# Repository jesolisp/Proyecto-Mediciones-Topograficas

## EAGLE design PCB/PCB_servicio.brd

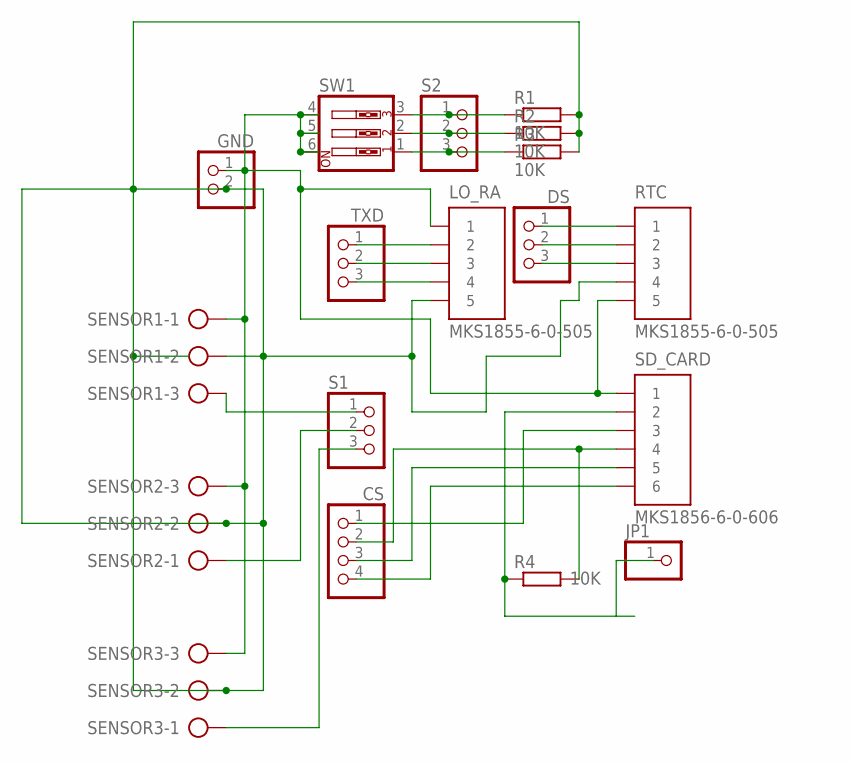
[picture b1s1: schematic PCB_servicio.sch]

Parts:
CS: PINHD-1X4; 1X04
DS: PINHD-1X3; 1X03
GND: PINHD-1X2; 1X02
JP1: PINHD-1X1; 1X01
LO_RA: MKS1855-6-0-505
R1, R2, R3, R4: 10K; 0207/12
RTC: MKS1855-6-0-505
S1, S2: PINHD-1X3; 1X03
SD_CARD: MKS1856-6-0-606
SENSOR1, SENSOR2, SENSOR3: AK500/3
SW1: SW_DIP-3; EDG-03
TXD: PINHD-1X3; 1X03

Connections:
unnamed: GND.1, LO_RA.1, RTC.5, SD_CARD.1, SENSOR1.1, SENSOR2.3, SENSOR3.3, SW1.4, SW1.5, SW1.6
unnamed: GND.2, LO_RA.5, R1.2, R2.2, R3.2, RTC.4, SENSOR1.2, SENSOR2.2, SENSOR3.2
unnamed: S1.1, SENSOR1.3
unnamed: S1.2, SENSOR2.1
unnamed: S1.3, SENSOR3.1
unnamed: R1.1, S2.1, SW1.3
unnamed: R2.1, S2.2, SW1.2
unnamed: R3.1, S2.3, SW1.1
unnamed: LO_RA.2, TXD.1
unnamed: LO_RA.3, TXD.2
unnamed: LO_RA.4, TXD.3
unnamed: CS.3, SD_CARD.5
unnamed: CS.4, SD_CARD.6
unnamed: CS.2, R4.2, SD_CARD.4
unnamed: CS.1, SD_CARD.3
unnamed: JP1.1, R4.1, SD_CARD.2
unnamed: DS.1, RTC.1
unnamed: DS.2, RTC.2
unnamed: DS.3, RTC.3

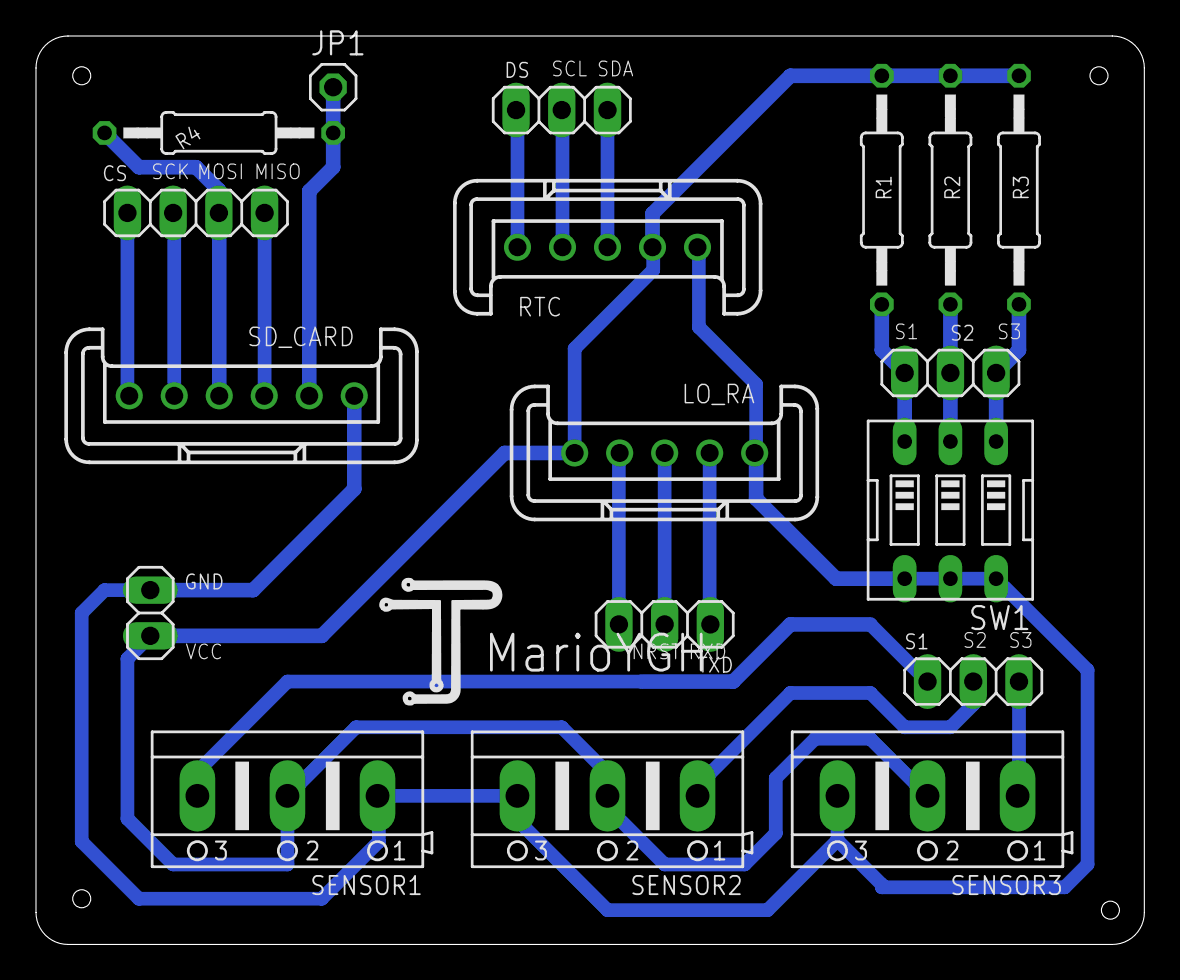
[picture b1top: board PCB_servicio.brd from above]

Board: 2 copper layers, 61.6 x 50.5 mm, 18 parts (0 on the bottom side), 19 nets.

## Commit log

2025-01-29 Rename completo.c to Envia_completo.c
2025-01-29 Create 2_SensoresySleep
2025-01-29 Rename 1_3sensores.c to 1_Sensores.c
2025-01-29 Update 2_SensoresySleep
